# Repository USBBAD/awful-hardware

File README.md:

# WTF?

Who the hell needs to build a bad USB microphone, when you can buy a goodo uno, cheapo and easo? No entiendo...

# Revision changelog

## 0.1 

- A completely working mic amplifier

## Next

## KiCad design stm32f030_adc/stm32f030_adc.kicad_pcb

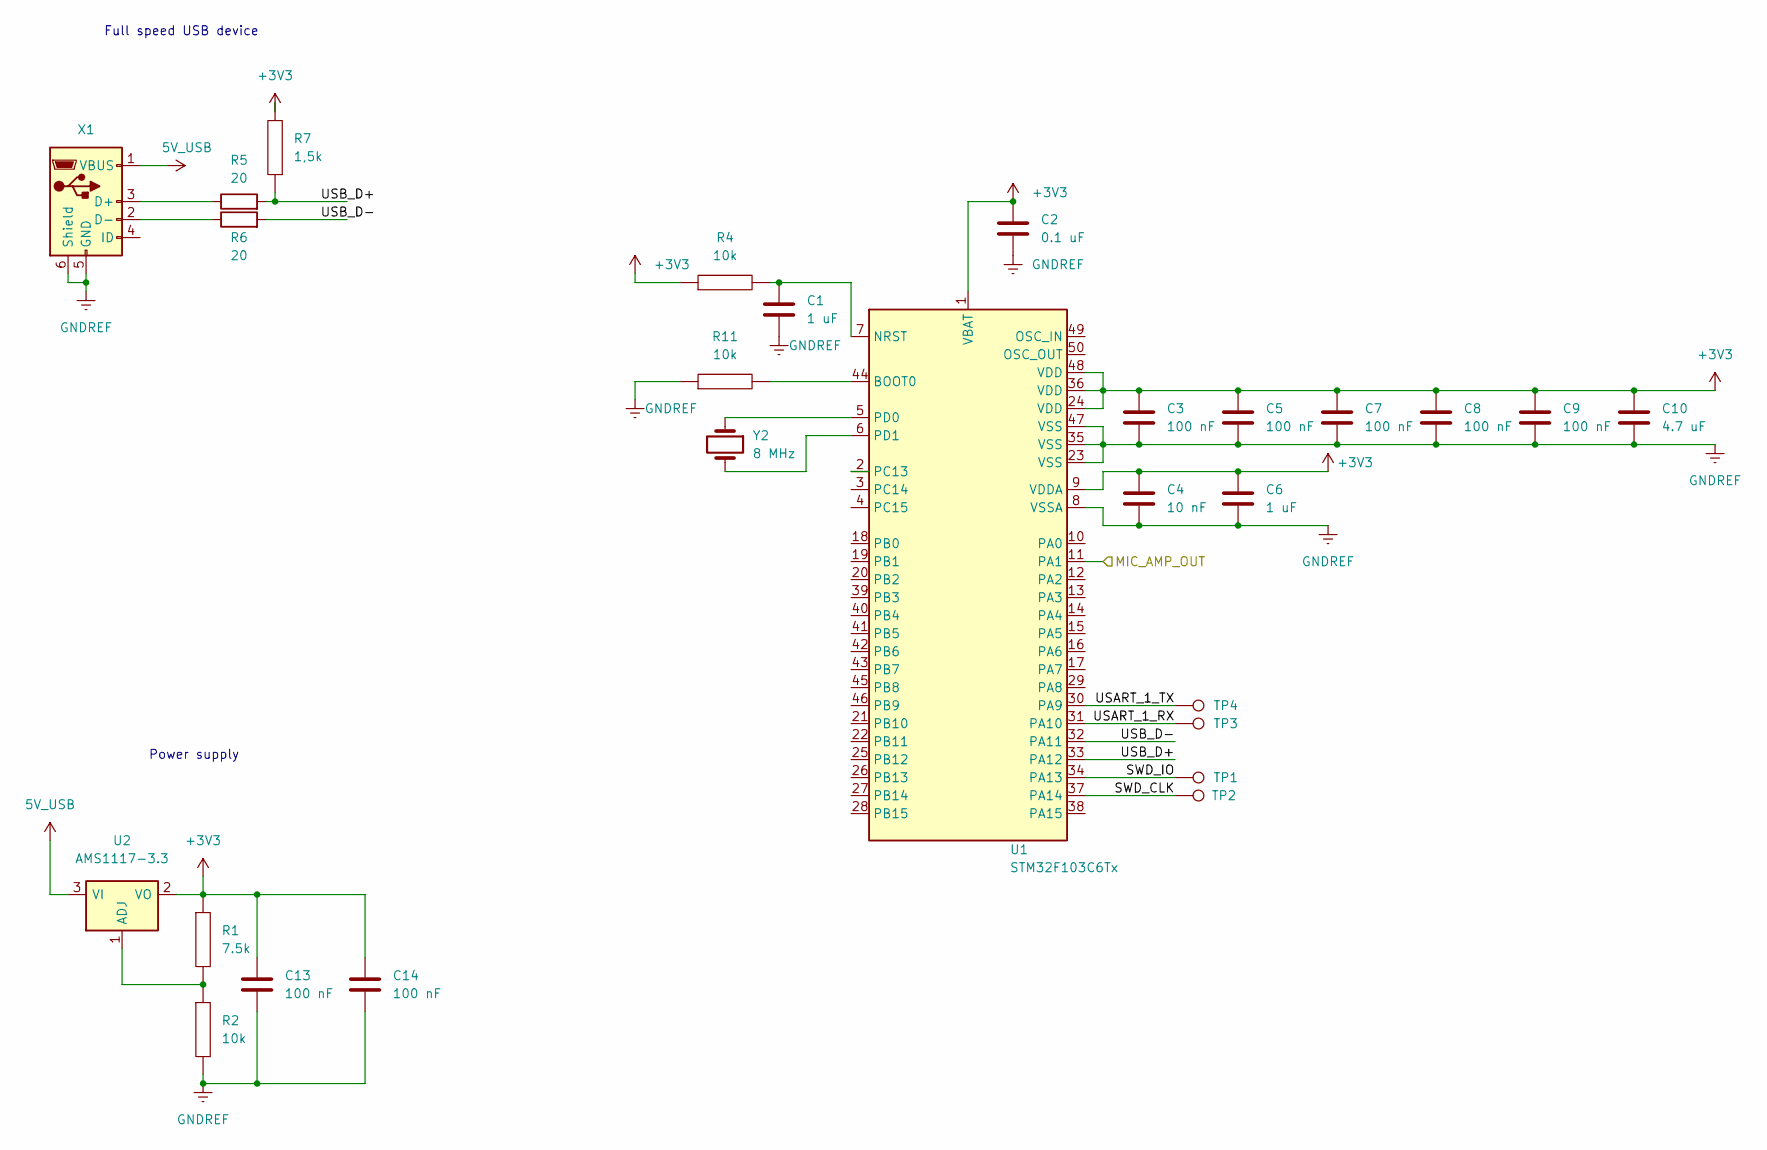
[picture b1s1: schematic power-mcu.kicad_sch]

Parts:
C1, C6: 1 uF; C_Disc_D4.7mm_W2.5mm_P5.00mm
C2: 0.1 uF; C_Disc_D4.7mm_W2.5mm_P5.00mm
C3, C5, C7, C8, C9, C13, C14: 100 nF; C_Disc_D4.7mm_W2.5mm_P5.00mm
C4: 10 nF; C_Disc_D4.7mm_W2.5mm_P5.00mm
C10: 4.7 uF; C_Disc_D4.7mm_W2.5mm_P5.00mm
R1: 7.5k; R_Axial_DIN0207_L6.3mm_D2.5mm_P10.16mm_Horizontal
R2, R4, R11: 10k; R_Axial_DIN0207_L6.3mm_D2.5mm_P10.16mm_Horizontal
R5, R6: 20; R_Axial_DIN0207_L6.3mm_D2.5mm_P10.16mm_Horizontal
R7: 1,5k; R_Axial_DIN0207_L6.3mm_D2.5mm_P10.16mm_Horizontal
TP1, TP2, TP3, TP4: TestPoint; TestPoint_Pad_D2.0mm
U1: STM32F103C6Tx; LQFP-48_7x7mm_P0.5mm
U2: AMS1117-3.3; SOT-223-3_TabPin2
X1: USB_B_Micro; USB_Mini-B_Lumberg_2486_01_Horizontal
Y2: 8 MHz; Resonator-2Pin_W6.0mm_H3.0mm

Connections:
5V_USB: U2.3 (VI), X1.1 (VBUS)
+3V3: C2.1, C3.1, C4.1, C5.1, C6.1, C7.1, C8.1, C9.1, C10.1, C13.1, C14.1, R1.1, R4.1, R7.2, U1.1 (VBAT), U1.9 (VDDA), U1.24 (VDD), U1.36 (VDD), U1.48 (VDD), U2.2 (VO); also elsewhere on the board
/Electret AMP/MIC_AMP_OUT: U1.11 (PA1); also elsewhere on the board
/Power and MCU/SWD_CLK: TP2.1, U1.37 (PA14)
/Power and MCU/SWD_IO: TP1.1, U1.34 (PA13)
/Power and MCU/USART_1_RX: TP3.1, U1.31 (PA10)
/Power and MCU/USART_1_TX: TP4.1, U1.30 (PA9)
/Power and MCU/USB_D+: R5.2, R7.1, U1.33 (PA12)
/Power and MCU/USB_D-: R6.2, U1.32 (PA11)
GNDREF: C1.2, C2.2, C3.2, C4.2, C5.2, C6.2, C7.2, C8.2, C9.2, C10.2, C13.2, C14.2, R2.2, R11.1, U1.8 (VSSA), U1.23 (VSS), U1.35 (VSS), U1.47 (VSS), X1.5 (GND), X1.6 (Shield); also elsewhere on the board
unnamed: R11.2, U1.44 (BOOT0)
unnamed: C1.1, R4.2, U1.7 (NRST)
unnamed: U1.5 (PD0), Y2.1
unnamed: U1.6 (PD1), Y2.2
unnamed: R1.2, R2.1, U2.1 (ADJ)
unnamed: R5.1, X1.3 (D+)
unnamed: R6.1, X1.2 (D-)

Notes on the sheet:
Full speed USB device
Power supply

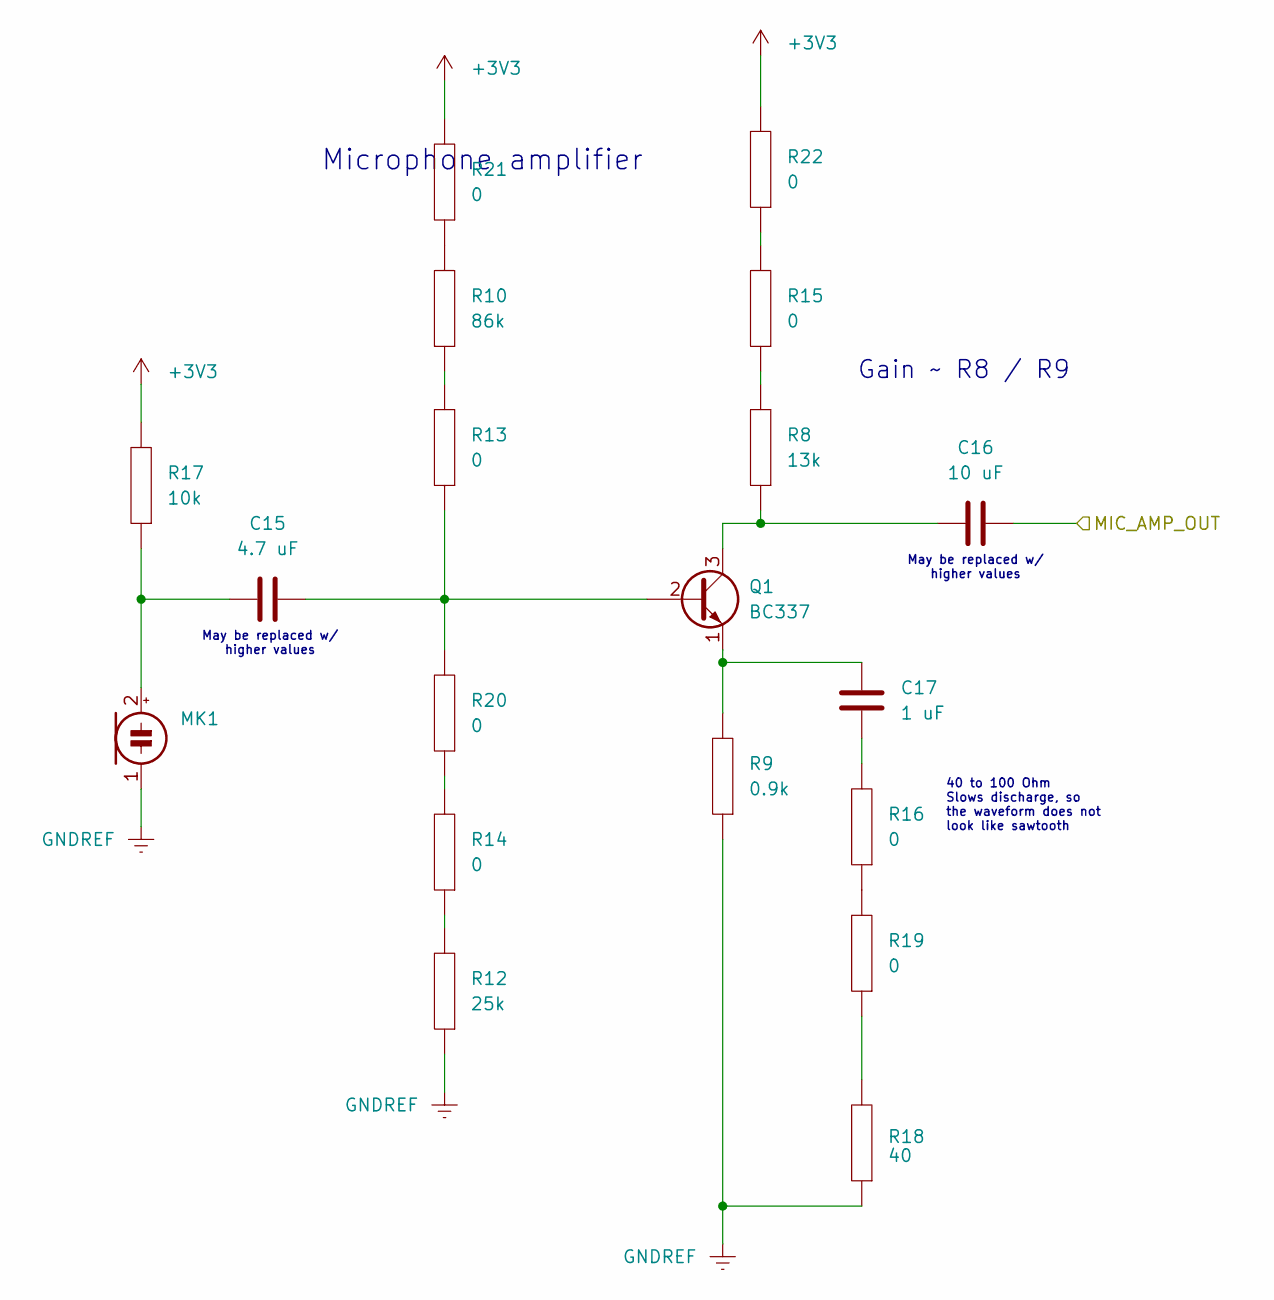
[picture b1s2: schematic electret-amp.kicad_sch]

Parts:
C15: 4.7 uF; CP_Radial_D8.0mm_P3.80mm
C16: 10 uF; CP_Radial_D8.0mm_P3.80mm
C17: 1 uF; CP_Radial_D8.0mm_P3.80mm
MK1: PinSocket_1x02_P2.00mm_Vertical
Q1: BC337; TO-92_Inline
R8: 13k; R_Axial_DIN0207_L6.3mm_D2.5mm_P10.16mm_Horizontal
R9: 0.9k; R_Axial_DIN0207_L6.3mm_D2.5mm_P10.16mm_Horizontal
R10: 86k; R_Axial_DIN0207_L6.3mm_D2.5mm_P10.16mm_Horizontal
R12: 25k; R_Axial_DIN0207_L6.3mm_D2.5mm_P10.16mm_Horizontal
R13, R14, R15, R16, R19, R20, R21, R22: 0; R_Axial_DIN0207_L6.3mm_D2.5mm_P10.16mm_Horizontal
R17: 10k; R_Axial_DIN0207_L6.3mm_D2.5mm_P10.16mm_Horizontal
R18: 40; R_Axial_DIN0207_L6.3mm_D2.5mm_P10.16mm_Horizontal

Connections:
+3V3: R17.2, R21.2, R22.2; also elsewhere on the board
/Electret AMP/MIC_AMP_OUT: C16.2; also elsewhere on the board
GNDREF: MK1.1 (-), R9.1, R12.1, R18.1; also elsewhere on the board
unnamed: C17.1, R16.2
unnamed: C15.1, MK1.2 (+), R17.1
unnamed: C15.2, Q1.2 (B), R13.1, R20.2
unnamed: C16.1, Q1.3 (C), R8.1
unnamed: C17.2, Q1.1 (E), R9.2
unnamed: R10.1, R13.2
unnamed: R10.2, R21.1
unnamed: R12.2, R14.1
unnamed: R14.2, R20.1
unnamed: R8.2, R15.1
unnamed: R15.2, R22.1
unnamed: R16.1, R19.2
unnamed: R18.2, R19.1

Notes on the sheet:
40 to 100 Ohm Slows discharge, so the waveform does not look like sawtooth
May be replaced w/ higher values
Microphone amplifier
Gain ~ R8 / R9

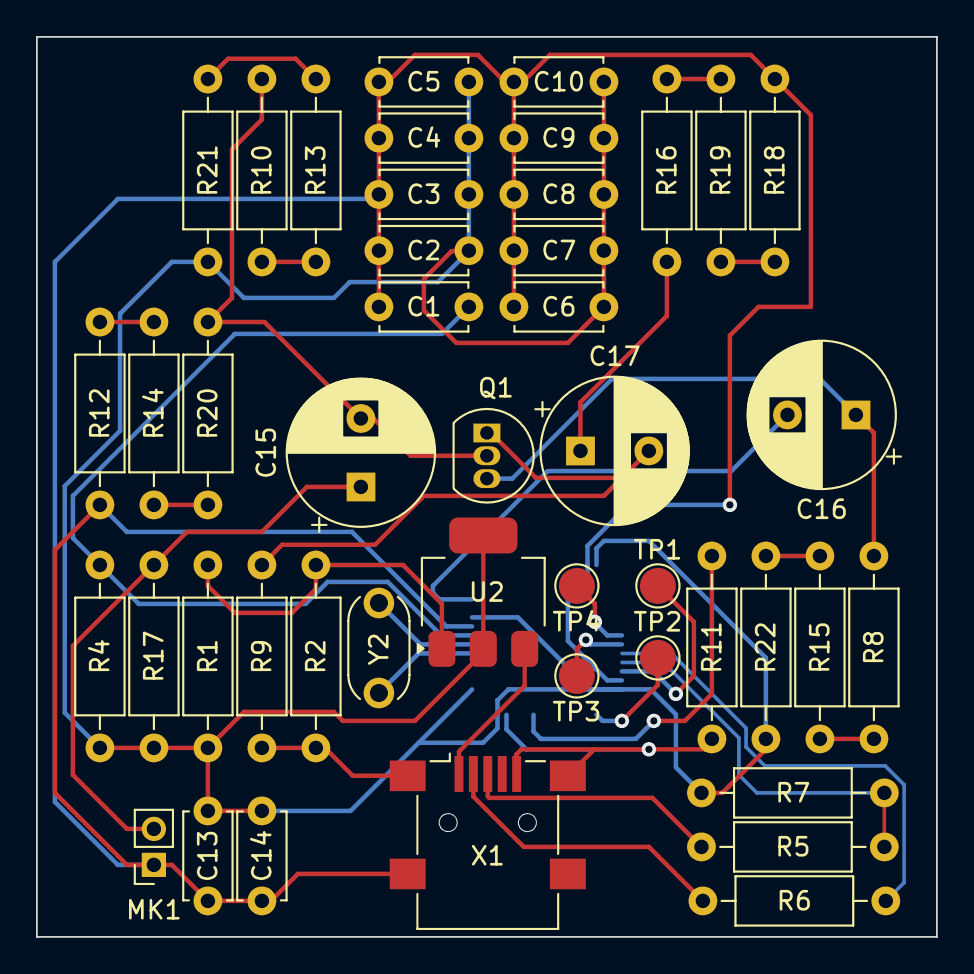
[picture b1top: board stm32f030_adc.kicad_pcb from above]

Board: 2 copper layers, 50.0 x 50.0 mm, 46 parts (1 on the bottom side), 30 nets.

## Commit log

2024-09-19 Initial
2024-09-19 [stm32f030_adc] Bug | USB D+ pull-ups, filtering caps for AMS-1117, external 8MHz oscillator
2024-10-17 [tools] Impl | Some calculators
2024-10-17 Added gitignore
2024-10-17 [schematics] Impl | Replaced OpAmp w/ BJT-based amplifier (not biased yet), reorganized sheets: separated MCU from gain, added hierarchical connections
2024-10-19 [tools bjt-amp-simulation lepton-geda-mic-amplifier] Impl | BJT calculator, KiCad+SPICE-based BJT amplifier simulation
2024-10-24 [bjt-amp-calc bjt-amp-simulation schematics] Impl | Validated amplifier design
2024-10-26 [schematics] Enh | Verified microphone design on a prototype hardware, adjusted mic. power resistance
2024-10-26 [README] Doc | Description, changelog
2024-11-30 [schematics] Bug | Wrong resistor values to offset the gate
2024-11-30 [bjt-amp-calc] Impl | BJT biasing calculator for the desired gain
2024-11-30 [.gitignore] Build |
2024-12-28 [bjt-amp-calc schematics] Enh | Modified consulting the prototype
2024-12-28 Assigned footprints, removed obsolete parts
2024-12-28 Layout: first approximation (grouping)
2024-12-30 [schematics] Build | Changed oscillator type, fixed unconnected lines, made some layout
2024-12-30 [schematics] Impl | Most of the work is done. Intermediate result
2024-12-31 Layout: cleaner version (intermediate)
2024-12-31 Layout: 1-layer board, done, first approximation
2024-12-31 Layout: fixed unconnected items (except for the LDO which should not have the connection anyway)
2024-12-31 Layout: GNDREF at the perimeter of the board:x
2024-12-31 Furhter fixes: added jumper for 3V3
2024-12-31 [schematics] Impl | Extensibility: more 0-jumpers
2024-12-31 Extensibility: more jumpers, intermediate result, the layout is not complete
2024-12-31 Esthetics: jumpers
2024-12-31 Esthetics: placement
2024-12-31 Layout: done w/ placement, and extensions
2024-12-31 Dimensions: narrower
2024-12-31 Narrowed
2025-01-01 Ref: dead line
2025-03-31 INTERMEDIATE
2025-04-05 [schematics] Impl | Finished placement on "Vert" version
2025-04-05 [schematics] Impl | Added DRC exclusions: unconnected grounds (it will be connected, because the USB shield is connected to the ground
